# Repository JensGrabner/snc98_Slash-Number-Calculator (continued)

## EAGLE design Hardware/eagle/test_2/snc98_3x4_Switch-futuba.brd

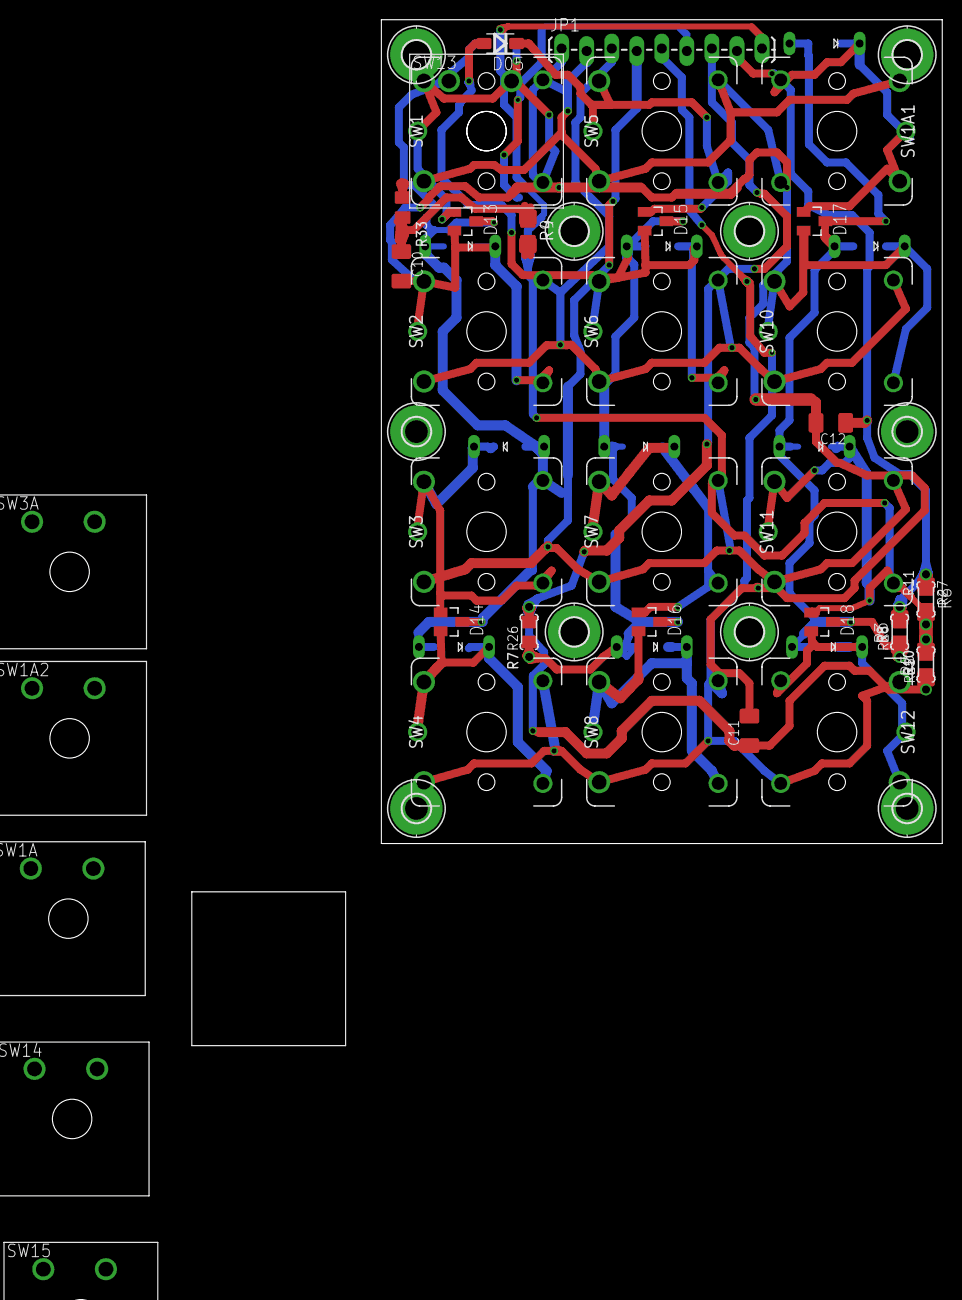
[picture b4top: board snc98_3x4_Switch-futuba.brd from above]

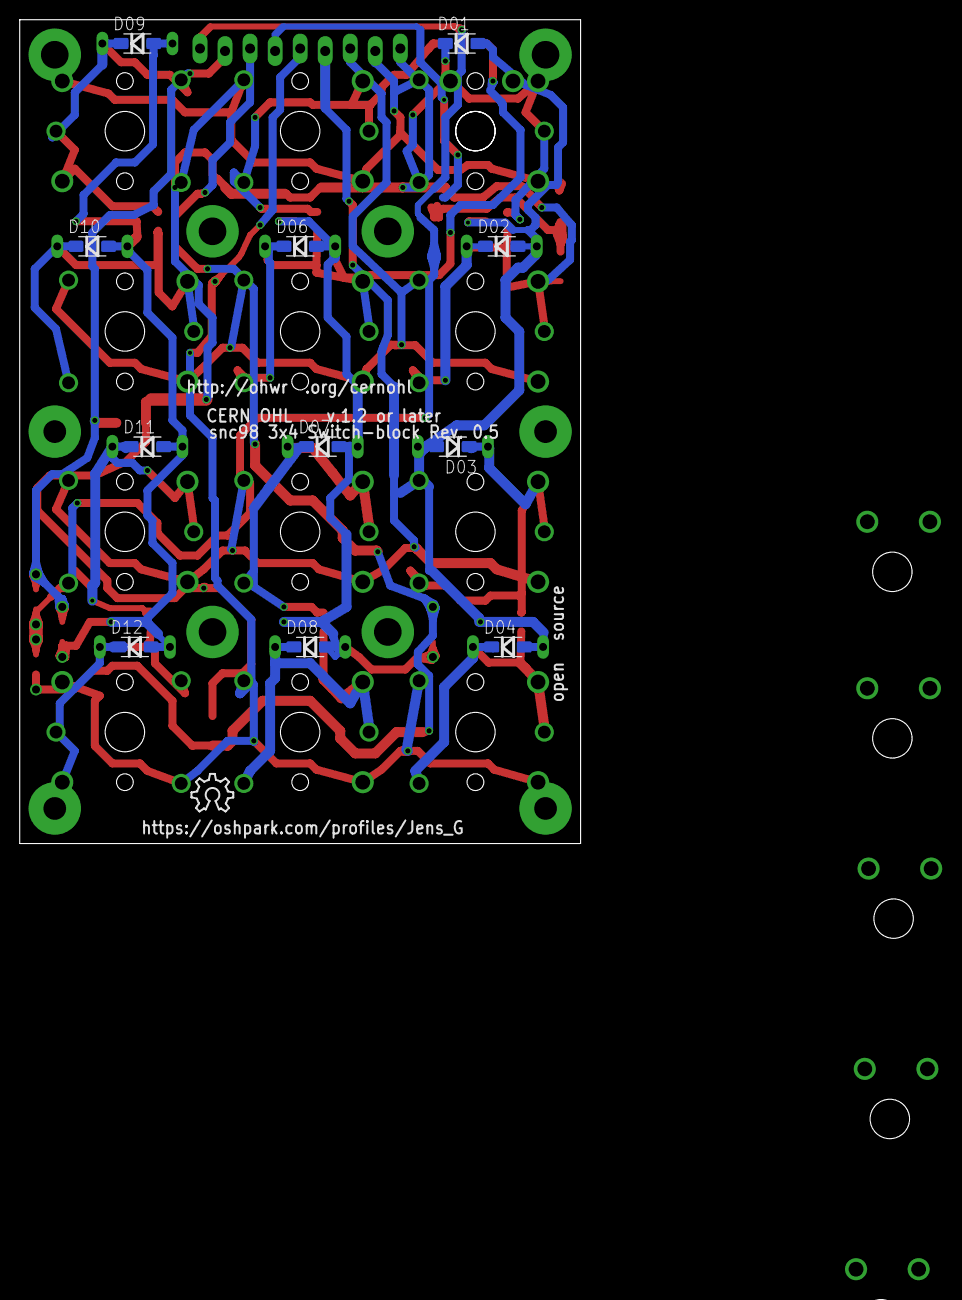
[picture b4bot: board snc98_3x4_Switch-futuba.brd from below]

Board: 2 copper layers, 56.9 x 83.6 mm, 75 parts (12 on the bottom side), 24 nets.

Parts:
C10, C11, C12: 15n; C1206K
D01, D02, D03, D04, D05, D06, D07, D08, D09: SD103AW-DIO; SOD-123F
D10, D11, D12: SD103CW; SOD-123F
D13, D14, D15, D16, D17, D18: BAT54A; SOT23
D19, D20, D21, D22, D23, D24, D25, D26, D27, D28: SD103C; 280MIL-TH
H1, H4, H5, H6, H7, H8: MOUNT-PAD-ROUND2.8; 2,8-PAD
H2, H3, H9, H10: MOUNT-PAD-ROUND2.3; 2,3-PAD
JP1: M09LOCK-LONGPADS; 1X09_LOCK_LONGPADS
LOGO1: OSHW_LOGO_8MILX0150-NT; OSHW_8X150_NOTEXT
R3: 6k8; R1206
R4, R5, R6: 27k; R1206
R7, R8, R33: 6k8; M0805
R9, R10, R11: 27k; M0805
R25, R27: 27k; 0204/5
R26, R28: 6k8; 0204/5
SW1, SW1A1, SW2, SW3, SW4, SW5, SW6, SW7, SW8, SW10, SW11, SW12: CHERRY_MX_WITH_FIXING_PINS; MX1A-XXNW
SW1A, SW1A2, SW3A, SW13, SW14, SW15: CHERRY_MX; MX1A-XXNN

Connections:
A2: C11.1, JP1.7, R5.1, R7.2, R10.1, R25.1, R26.2
A3: C12.1, JP1.8, R3.2, R6.1, R8.2, R11.1, R27.1, R28.2
AREF: R5.2, R6.2, R10.2, R11.2, R25.2, R27.2
A_2: D05.A, D06.A, D07.A, D08.A, D15.3, D16.3, D22.P$1, D23.P$1, D24.P$1, R7.1, R26.1
A_3: D09.A, D10.A, D11.A, D12.A, D17.3, D18.3, D25.P$1, D26.P$1, D27.P$1, D28.P$1, R3.1, R8.1, R28.1
C1: JP1.2, SW1.1, SW1.3, SW1A1.1, SW1A1.3, SW5.1, SW5.3
C2: JP1.3, SW2.1, SW2.3, SW6.1, SW6.3, SW10.1, SW10.3
C3: JP1.4, SW3.1, SW3.3, SW7.1, SW7.3, SW11.1, SW11.3
C4: JP1.5, SW4.1, SW4.3, SW8.1, SW8.3, SW12.1, SW12.3
GND: C10.2, C11.2, C12.2, JP1.1
unnamed: D04.C, D14.2, D21.P$2, SW4.2, SW4.4, SW4.5
unnamed: D01.C, D13.1, SW1.2, SW1.4, SW1.5
unnamed: D09.C, D17.1, D25.P$2, SW1A1.2, SW1A1.4, SW1A1.5
unnamed: D10.C, D17.2, D26.P$2, SW10.2, SW10.4, SW10.5
unnamed: D02.C, D13.2, D19.P$2, SW2.2, SW2.4, SW2.5
unnamed: D11.C, D18.1, D27.P$2, SW11.2, SW11.4, SW11.5
unnamed: D12.C, D18.2, D28.P$2, SW12.2, SW12.4, SW12.5
unnamed: D05.C, D15.1, SW5.2, SW5.4, SW5.5
unnamed: D06.C, D15.2, D22.P$2, SW6.2, SW6.4, SW6.5
unnamed: D07.C, D16.1, D23.P$2, SW7.2, SW7.4, SW7.5
unnamed: D08.C, D16.2, D24.P$2, SW8.2, SW8.4, SW8.5
unnamed: D03.C, D14.1, D20.P$2, SW3.2, SW3.4, SW3.5
S$5: JP1.9, R4.2
S$9: D02.A, D03.A, D04.A, D13.3, D14.3, D19.P$1, D20.P$1, D21.P$1

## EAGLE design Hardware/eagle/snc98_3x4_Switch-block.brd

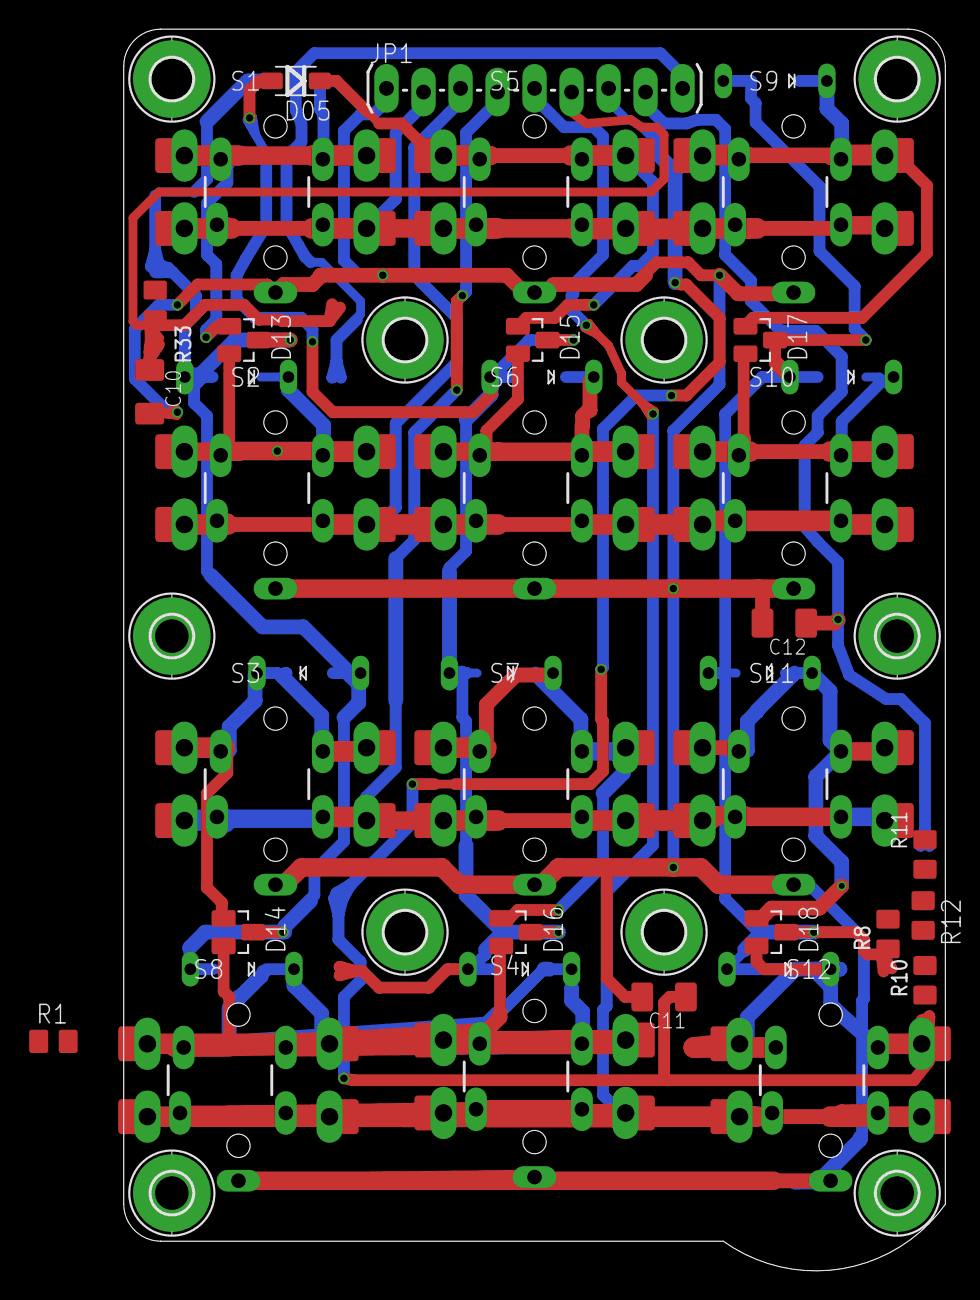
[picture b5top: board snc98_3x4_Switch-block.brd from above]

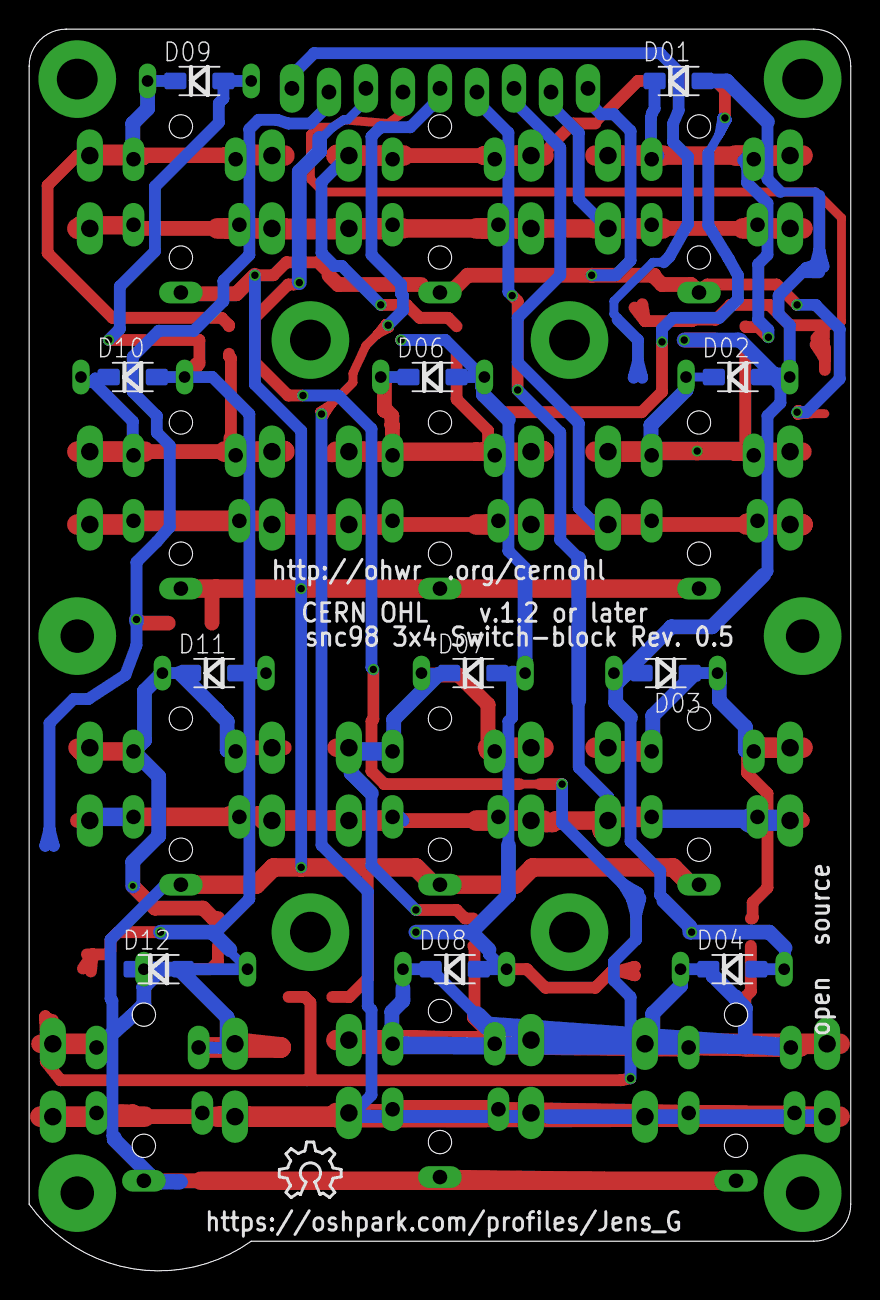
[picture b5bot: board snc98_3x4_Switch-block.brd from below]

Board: 2 copper layers, 56.4 x 85.2 mm, 61 parts (12 on the bottom side), 24 nets.

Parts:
C10, C11, C12: 15n; C1206K
D01, D02, D03, D04, D05, D06, D07, D08, D09: SD103AW-DIO; SOD-123F
D10, D11, D12: SD103CW; SOD-123F
D13, D14, D15, D16, D17, D18: BAT54A; SOT23
D19, D20, D21, D22, D23, D24, D25, D26, D27, D28: SD103C; 280MIL-TH
H1, H4, H5, H6, H7, H8: MOUNT-PAD-ROUND2.8; 2,8-PAD
H2, H3, H9, H10: MOUNT-PAD-ROUND2.3; 2,3-PAD
JP1: M09LOCK-LONGPADS; 1X09_LOCK_LONGPADS
LOGO1: OSHW_LOGO_8MILX0150-NT; OSHW_8X150_NOTEXT
R1, R8, R33: 6k8; M0805
R10, R11, R12: 27k; M0805
S1, S2, S3, S4, S5, S6, S7, S8, S9, S10, S11, S12: B3F-4150; TACTILE-PTH-12MM

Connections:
A1: C10.1, JP1.6, R12.1, R33.2
A2: C11.1, JP1.7, R1.2, R10.1
A3: C12.1, JP1.8, R8.2, R11.1
AREF: JP1.9, R10.2, R11.2, R12.2
A_1: D01.A, D02.A, D03.A, D04.A, D13.3, D14.3, D19.P$1, D20.P$1, D21.P$1, R33.1
A_2: D05.A, D06.A, D07.A, D08.A, D15.3, D16.3, D22.P$1, D23.P$1, D24.P$1, R1.1
A_3: D09.A, D10.A, D11.A, D12.A, D17.3, D18.3, D25.P$1, D26.P$1, D27.P$1, D28.P$1, R8.1
C1: JP1.2, S1.P$1, S1.P$2, S1.P$11, S1.P$12, S1.P$21, S1.P$22, S5.P$1, S5.P$2, S5.P$11, S5.P$12, S5.P$21, S5.P$22, S9.P$1, S9.P$2, S9.P$11, S9.P$12, S9.P$21, S9.P$22
C2: JP1.3, S2.P$1, S2.P$2, S2.P$11, S2.P$12, S2.P$21, S2.P$22, S6.P$1, S6.P$2, S6.P$11, S6.P$12, S6.P$21, S6.P$22, S10.P$1, S10.P$2, S10.P$11, S10.P$12, S10.P$21, S10.P$22
C3: JP1.4, S3.P$1, S3.P$2, S3.P$11, S3.P$12, S3.P$21, S3.P$22, S7.P$1, S7.P$2, S7.P$11, S7.P$12, S7.P$21, S7.P$22, S11.P$1, S11.P$2, S11.P$11, S11.P$12, S11.P$21, S11.P$22
C4: JP1.5, S4.P$1, S4.P$2, S4.P$11, S4.P$12, S4.P$21, S4.P$22, S8.P$1, S8.P$2, S8.P$11, S8.P$12, S8.P$21, S8.P$22, S12.P$1, S12.P$2, S12.P$11, S12.P$12, S12.P$21, S12.P$22
GND: C10.2, C11.2, C12.2, JP1.1, S1.P$15, S2.P$15, S3.P$15, S4.P$15, S5.P$15, S6.P$15, S7.P$15, S8.P$15, S9.P$15, S10.P$15, S11.P$15, S12.P$15
unnamed: D04.C, D14.2, D21.P$2, S4.P$3, S4.P$4, S4.P$13, S4.P$14, S4.P$23, S4.P$24
unnamed: D01.C, D13.1, S1.P$3, S1.P$4, S1.P$13, S1.P$14, S1.P$23, S1.P$24
unnamed: D09.C, D17.1, D25.P$2, S9.P$3, S9.P$4, S9.P$13, S9.P$14, S9.P$23, S9.P$24
unnamed: D10.C, D17.2, D26.P$2, S10.P$3, S10.P$4, S10.P$13, S10.P$14, S10.P$23, S10.P$24
unnamed: D02.C, D13.2, D19.P$2, S2.P$3, S2.P$4, S2.P$13, S2.P$14, S2.P$23, S2.P$24
unnamed: D11.C, D18.1, D27.P$2, S11.P$3, S11.P$4, S11.P$13, S11.P$14, S11.P$23, S11.P$24
unnamed: D12.C, D18.2, D28.P$2, S12.P$3, S12.P$4, S12.P$13, S12.P$14, S12.P$23, S12.P$24
unnamed: D05.C, D15.1, S5.P$3, S5.P$4, S5.P$13, S5.P$14, S5.P$23, S5.P$24
unnamed: D06.C, D15.2, D22.P$2, S6.P$3, S6.P$4, S6.P$13, S6.P$14, S6.P$23, S6.P$24
unnamed: D07.C, D16.1, D23.P$2, S7.P$3, S7.P$4, S7.P$13, S7.P$14, S7.P$23, S7.P$24
unnamed: D08.C, D16.2, D24.P$2, S8.P$3, S8.P$4, S8.P$13, S8.P$14, S8.P$23, S8.P$24
unnamed: D03.C, D14.1, D20.P$2, S3.P$3, S3.P$4, S3.P$13, S3.P$14, S3.P$23, S3.P$24

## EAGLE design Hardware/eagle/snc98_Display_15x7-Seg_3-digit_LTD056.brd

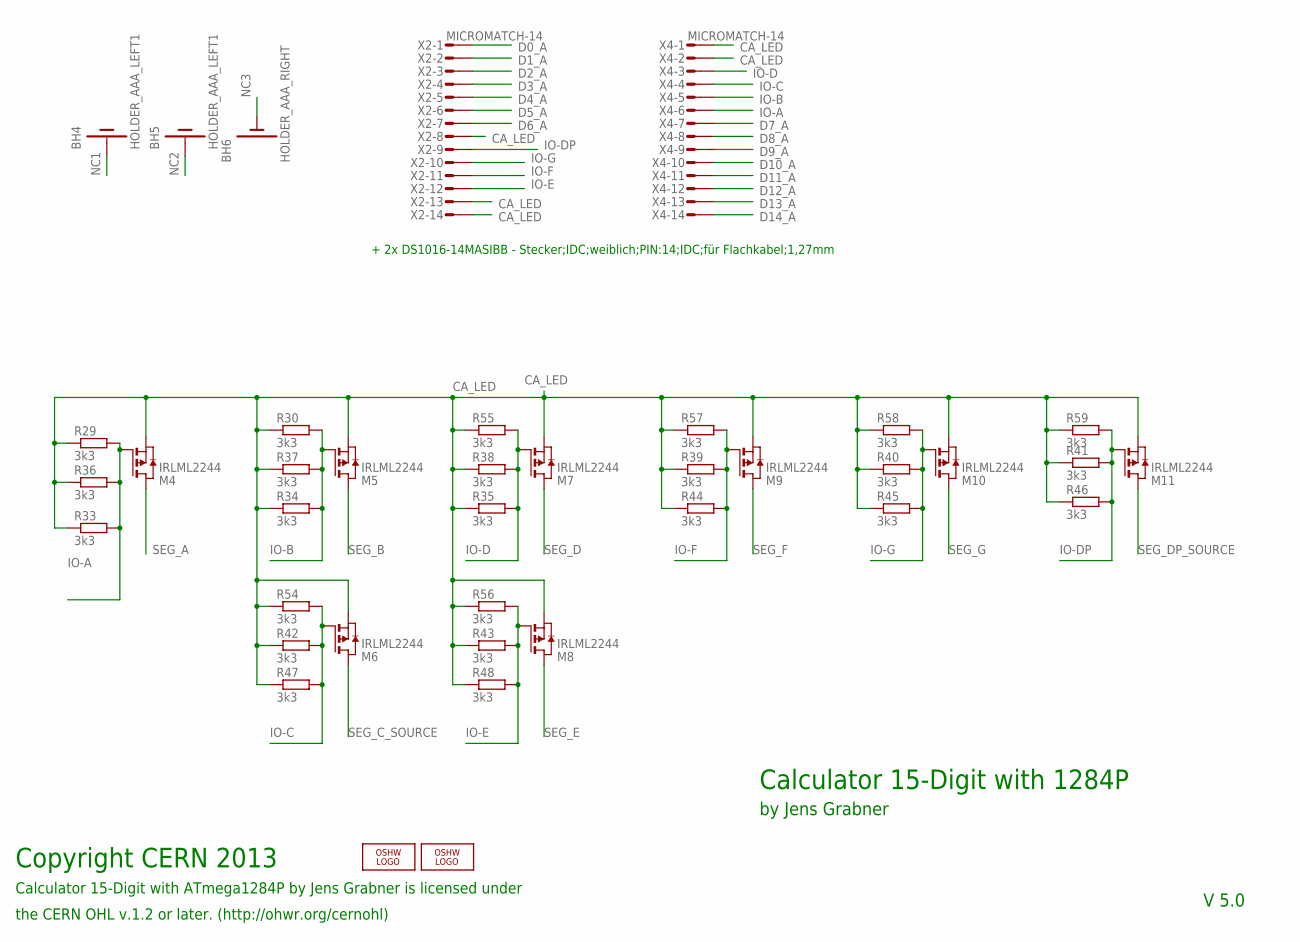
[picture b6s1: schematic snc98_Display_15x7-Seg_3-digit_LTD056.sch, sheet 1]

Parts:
BH4, BH5: HOLDER_AAA_LEFT1; BATTERY-AAA-LEFT
BH6: HOLDER_AAA_RIGHT; BATTERY-AAA-RIGHT
LOGO1: OSHW_LOGO_8MILX0150-NT; OSHW_8X150_NOTEXT
LOGO3: OSHW_LOGO_6MILX0100-NT; OSHW_6X100_NOTEXT
M4, M5, M6, M7, M8, M9, M10, M11: IRLML2244; SOT-23; MPN IRLML2244TRPBF
R29, R30, R54, R55, R56, R57, R58, R59: 3k3; 0204/5
R33, R34, R35, R44, R45, R46, R47, R48: 3k3; M0805
R36, R37, R38, R39, R40, R41, R42, R43: 3k3; R1206
X2, X4: MICROMATCH-14

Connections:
CA_LED: M4.2 (S), M5.2 (S), M6.2 (S), M7.2 (S), M8.2 (S), M9.2 (S), M10.2 (S), M11.2 (S), R29.1, R30.1, R33.1, R34.1, R35.1, R36.1, R37.1, R38.1, R39.1, R40.1, R41.1, R42.1, R43.1, R44.1, R45.1, R46.1, R47.1, R48.1, R54.1, R55.1, R56.1, R57.1, R58.1, R59.1, X2.8, X2.13, X2.14, X4.1, X4.2; also elsewhere on the board
D0_A: X2.1; also elsewhere on the board
D1_A: X2.2; also elsewhere on the board
D2_A: X2.3; also elsewhere on the board
D3_A: X2.4; also elsewhere on the board
D4_A: X2.5; also elsewhere on the board
D5_A: X2.6; also elsewhere on the board
D6_A: X2.7; also elsewhere on the board
D7_A: X4.7; also elsewhere on the board
D8_A: X4.8; also elsewhere on the board
D9_A: X4.9; also elsewhere on the board
D10_A: X4.10; also elsewhere on the board
D11_A: X4.11; also elsewhere on the board
D12_A: X4.12; also elsewhere on the board
D13_A: X4.13; also elsewhere on the board
D14_A: X4.14; also elsewhere on the board
IO-A: M4.1 (G), R29.2, R33.2, R36.2, X4.6
IO-B: M5.1 (G), R30.2, R34.2, R37.2, X4.5
IO-C: M6.1 (G), R42.2, R47.2, R54.2, X4.4
IO-D: M7.1 (G), R35.2, R38.2, R55.2, X4.3
IO-DP: M11.1 (G), R41.2, R46.2, R59.2, X2.9
IO-E: M8.1 (G), R43.2, R48.2, R56.2, X2.12
IO-F: M9.1 (G), R39.2, R44.2, R57.2, X2.11
IO-G: M10.1 (G), R40.2, R45.2, R58.2, X2.10
NC1: BH4.P1, BH4.P2, BH4.P3, BH4.P4
NC2: BH5.P1, BH5.P2, BH5.P3, BH5.P4
NC3: BH6.M1, BH6.M2, BH6.M3, BH6.M4
SEG_A: M4.3 (D); also elsewhere on the board
SEG_B: M5.3 (D); also elsewhere on the board
SEG_C_SOURCE: M6.3 (D); also elsewhere on the board
SEG_D: M7.3 (D); also elsewhere on the board
SEG_DP_SOURCE: M11.3 (D)
SEG_E: M8.3 (D); also elsewhere on the board
SEG_F: M9.3 (D); also elsewhere on the board
SEG_G: M10.3 (D); also elsewhere on the board

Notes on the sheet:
Calculator 15-Digit with 1284P
by Jens Grabner
V 5.0
Calculator 15-Digit with ATmega1284P by Jens Grabner is licensed under
Copyright CERN 2013
the CERN OHL v.1.2 or later. (http://ohwr.org/cernohl)
+ 2x DS1016-14MASIBB - Stecker;IDC;weiblich;PIN:14;IDC;für Flachkabel;1,27mm

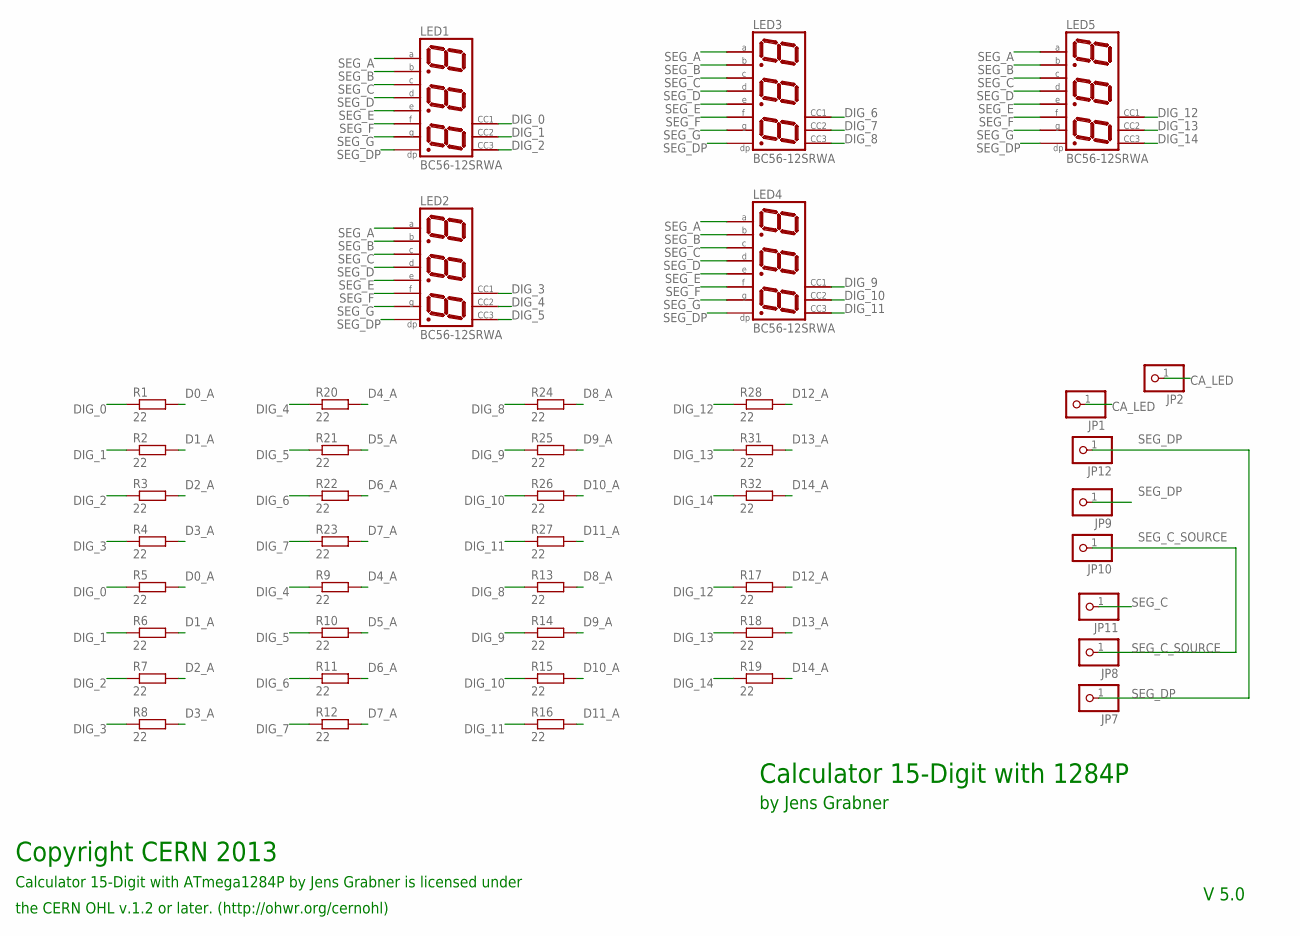
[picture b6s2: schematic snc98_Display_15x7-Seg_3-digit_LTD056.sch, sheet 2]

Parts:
JP1, JP2, JP7, JP8, JP9, JP10, JP11, JP12: PINHD-1X1; 1X01
LED1, LED2, LED3, LED4, LED5: BC56-12SRWA; BX56-12
R1, R2, R3, R4, R20, R21, R22, R23, R24, R25, R26, R27, R28, R31, R32: 22; R0805
R5, R6, R7, R8, R9, R10, R11, R12, R13, R14, R15, R16, R17, R18, R19: 22; R1210

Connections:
CA_LED: JP1.1, JP2.1; also elsewhere on the board
D0_A: R1.2, R5.2; also elsewhere on the board
D1_A: R2.2, R6.2; also elsewhere on the board
D2_A: R3.2, R7.2; also elsewhere on the board
D3_A: R4.2, R8.2; also elsewhere on the board
D4_A: R9.2, R20.2; also elsewhere on the board
D5_A: R10.2, R21.2; also elsewhere on the board
D6_A: R11.2, R22.2; also elsewhere on the board
D7_A: R12.2, R23.2; also elsewhere on the board
D8_A: R13.2, R24.2; also elsewhere on the board
D9_A: R14.2, R25.2; also elsewhere on the board
D10_A: R15.2, R26.2; also elsewhere on the board
D11_A: R16.2, R27.2; also elsewhere on the board
D12_A: R17.2, R28.2; also elsewhere on the board
D13_A: R18.2, R31.2; also elsewhere on the board
D14_A: R19.2, R32.2; also elsewhere on the board
DIG_0: LED1.12 (CA), R1.1, R5.1
DIG_1: LED1.9 (CA), R2.1, R6.1
DIG_2: LED1.8 (CA), R3.1, R7.1
DIG_3: LED2.12 (CA), R4.1, R8.1
DIG_4: LED2.9 (CA), R9.1, R20.1
DIG_5: LED2.8 (CA), R10.1, R21.1
DIG_6: LED3.12 (CA), R11.1, R22.1
DIG_7: LED3.9 (CA), R12.1, R23.1
DIG_8: LED3.8 (CA), R13.1, R24.1
DIG_9: LED4.12 (CA), R14.1, R25.1
DIG_10: LED4.9 (CA), R15.1, R26.1
DIG_11: LED4.8 (CA), R16.1, R27.1
DIG_12: LED5.12 (CA), R17.1, R28.1
DIG_13: LED5.9 (CA), R18.1, R31.1
DIG_14: LED5.8 (CA), R19.1, R32.1
SEG_A: LED1.11 (A), LED2.11 (A), LED3.11 (A), LED4.11 (A), LED5.11 (A); also elsewhere on the board
SEG_B: LED1.7 (B), LED2.7 (B), LED3.7 (B), LED4.7 (B), LED5.7 (B); also elsewhere on the board
SEG_C: JP11.1, LED1.4 (C), LED2.4 (C), LED3.4 (C), LED4.4 (C), LED5.4 (C)
SEG_C_SOURCE: JP8.1, JP10.1; also elsewhere on the board
SEG_D: LED1.2 (D), LED2.2 (D), LED3.2 (D), LED4.2 (D), LED5.2 (D); also elsewhere on the board
SEG_DP: JP7.1, JP9.1, JP12.1, LED1.3 (DP), LED2.3 (DP), LED3.3 (DP), LED4.3 (DP), LED5.3 (DP)
SEG_E: LED1.1 (E), LED2.1 (E), LED3.1 (E), LED4.1 (E), LED5.1 (E); also elsewhere on the board
SEG_F: LED1.10 (F), LED2.10 (F), LED3.10 (F), LED4.10 (F), LED5.10 (F); also elsewhere on the board
SEG_G: LED1.5 (G), LED2.5 (G), LED3.5 (G), LED4.5 (G), LED5.5 (G); also elsewhere on the board

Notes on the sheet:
Calculator 15-Digit with 1284P
by Jens Grabner
V 5.0
Calculator 15-Digit with ATmega1284P by Jens Grabner is licensed under
Copyright CERN 2013
the CERN OHL v.1.2 or later. (http://ohwr.org/cernohl)

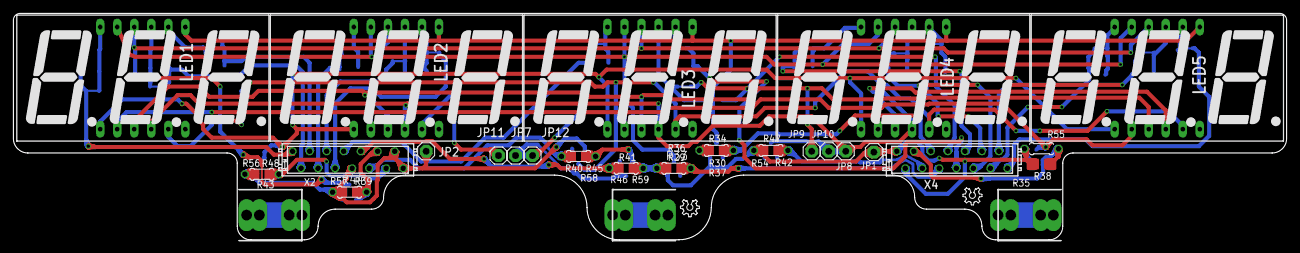
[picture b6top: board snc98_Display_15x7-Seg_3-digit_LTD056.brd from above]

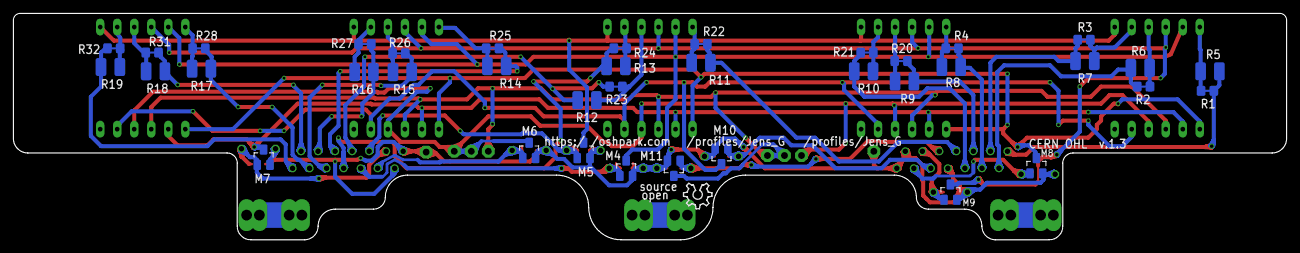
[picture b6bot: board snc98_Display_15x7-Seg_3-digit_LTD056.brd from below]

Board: 2 copper layers, 190.0 x 33.8 mm, 83 parts (39 on the bottom side), 51 nets.

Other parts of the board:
LOGO2: OSHW_LOGO_6MILX0100-NT; OSHW_6X100_NOTEXT

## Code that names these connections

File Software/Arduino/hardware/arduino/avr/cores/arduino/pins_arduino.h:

//
//
// Pins definitions for Goldilocks 1284P
// Original file from Maniacbug's Mighty-1284 core
// This version by Phillip Stevens (1st June 2013)
//
//

#ifndef Pins_Arduino_h
#define Pins_Arduino_h

#include <avr/pgmspace.h>

//                    ATMEL ATMEGA1284P on Goldilocks
//                    Actual implementation with VQFN
//
//                               +---\/---+
//            PCINT8 (D14) PB0  1|        |40  PA0 (AI 0 / D24) PCINT0
//            PCINT9 (D15) PB1  2|        |39  PA1 (AI 1 / D25) PCINT1
//      PCINT10/INT2 (D 8) PB2  3|        |38  PA2 (AI 2 / D26) PCINT2
//      PCINT11/OC0A*(D 9) PB3  4|        |37  PA3 (AI 3 / D27) PCINT3
//   PCINT12/0C0B/SS*(D10) PB4  5|        |36  PA4 (AI 4 / D28) PCINT4
//      PCINT13/MOSI (D11) PB5  6|        |35  PA5 (AI 5 / D29) PCINT5
// PCINT14/OC3A/MISO*(D12) PB6  7|        |34  PA6 (AI 6 / D30) PCINT6
//  PCINT15/OC3B/SCK*(D13) PB7  8|        |33  PA7 (AI 7 / D31) PCINT7
//                         RST  9|        |32  AREF
//                         VCC 10|        |31  GND 
//                         GND 11|        |30  AVCC
//                       XTAL2 12|        |29  PC7 (D23) TOSC2/PCINT23
//                       XTAL1 13|        |28  PC6 (D22) TOSC1/PCINT22
//       PCINT24/RX0 (D 0) PD0 14|        |27  PC5 (D21) TDI/PCINT21
//       PCINT25/TX0 (D 1) PD1 15|        |26  PC4 (D20) TDO/PCINT20
//  PCINT26/INT0/RX1 (D 2) PD2 16|        |25  PC3 (D19) TMS/PCINT19
//  PCINT27/INT1/TX1 (D 3) PD3 17|        |24  PC2 (D18) TCK/PCINT18
//      PCINT28/OC1B*(D 4) PD4 18|        |23  PC1 (D17) SDA/PCINT17
//      PCINT29/OC1A*(D 5) PD5 19|        |22  PC0 (D16) SCL/PCINT16
//      PCINT30/OC2B*(D 6) PD6 20|        |21  PD7 (D 7)*OC2A/PCINT31
//                               +--------+
// * = PWM capable pin
// TOSCn = RTC Crystal pinout
// TCK/TMS/TDO/TDI = JTAG pinout

/*                       
                         PCICR
   PCINT7-0:   D31-24  : bit 0   
   PCINT15-8:  D15- 8  : bit 1
   PCINT23-16: D23-16  : bit 2
   PCINT31-24: D 7- 0  : bit 3
*/

#define NUM_DIGITAL_PINS            32
#define NUM_ANALOG_INPUTS           8
#define analogInputToDigitalPin(p)  ((p < NUM_ANALOG_INPUTS) ? (p) + 24 : -1)

#define digitalPinHasPWM(p)         ((p) == 4 || (p) == 5 || (p) == 6 || (p) == 7 || (p) == 9 || (p) == 10 || (p) == 12 || (p) == 13)

static const uint8_t SS   = 10;
static const uint8_t MOSI = 11;
static const uint8_t MISO = 12;
static const uint8_t SCK  = 13;

static const uint8_t SDA = 17;
static const uint8_t SCL = 16;
static const uint8_t LED = 13;

static const uint8_t A0 = 24;
static const uint8_t A1 = 25;
static const uint8_t A2 = 26;
static const uint8_t A3 = 27;
static const uint8_t A4 = 28;
static const uint8_t A5 = 29;
static const uint8_t A6 = 30;
static const uint8_t A7 = 31;

#define digitalPinToPCICR(p)    (((p) >= 0 && (p) < NUM_DIGITAL_PINS) ? (&PCICR) : ((uint8_t *)0))
#define digitalPinToPCICRbit(p) (((p) <= 7) ? 3 : (((p) <= 15) ? 1 : (((p) <= 23) ? 2 : 0)))
#define digitalPinToPCMSK(p)    (((p) <= 7) ? (&PCMSK3) : (((p) <= 15) ? (&PCMSK1) : (((p) <= 23) ? (&PCMSK2) : (&PCMSK0) )))

// The special case here, created by keeping the SPI interface on Arduino Uno pin numbering.
#define digitalPinToPCMSKbit(p) (((p) > 7 && (p) < 16) ? (((p) < 14 ? (p)+2 : (p)-6) % 8) : ((p) % 8))

#ifdef ARDUINO_MAIN

#define PA 1
#define PB 2
#define PC 3
#define PD 4

// these arrays map port names (e.g. port B) to the
// appropriate addresses for various functions (e.g. reading
// and writing)
const uint16_t PROGMEM port_to_mode_PGM[] =
{
	NOT_A_PORT,
	(uint16_t) &DDRA,
	(uint16_t) &DDRB,
	(uint16_t) &DDRC,
	(uint16_t) &DDRD,
};

const uint16_t PROGMEM port_to_output_PGM[] =
{
	NOT_A_PORT,
	(uint16_t) &PORTA,
	(uint16_t) &PORTB,
	(uint16_t) &PORTC,
	(uint16_t) &PORTD,
};

const uint16_t PROGMEM port_to_input_PGM[] =
{
	NOT_A_PORT,
	(uint16_t) &PINA,
	(uint16_t) &PINB,
	(uint16_t) &PINC,
	(uint16_t) &PIND,
};

const uint8_t PROGMEM digital_pin_to_port_PGM[] =
{
	PD, /* 0 */
	PD,
	PD,
	PD,
	PD,
	PD,
	PD,
	PD,
	PB, /* 8 */
	PB,
	PB,
	PB,
	PB,
	PB,
	PB,
	PB,
	PC, /* 16 */
	PC,
	PC,
	PC,
	PC,
	PC,
   	PC,
	PC,
	PA, /* 24 */
	PA,
	PA,
	PA,
	PA,
	PA,
	PA,
	PA  /* 31 */
};

const uint8_t PROGMEM digital_pin_to_bit_mask_PGM[] =
{
	_BV(0), /* 0, port D */
	_BV(1),
	_BV(2),
	_BV(3),
	_BV(4),
	_BV(5),
	_BV(6),
	_BV(7),
	_BV(2), /* 8, port B */
	_BV(3),
	_BV(4),
	_BV(5),
	_BV(6),
	_BV(7),
	_BV(0),
	_BV(1),
	_BV(0), /* 16, port C */
	_BV(1),
	_BV(2),
	_BV(3),
	_BV(4),
	_BV(5),
	_BV(6),
	_BV(7),
	_BV(0), /* 24, port A */
	_BV(1),
	_BV(2),
	_BV(3),
	_BV(4),
	_BV(5),
	_BV(6),
	_BV(7)
};

const uint8_t PROGMEM digital_pin_to_timer_PGM[] =
{
	NOT_ON_TIMER, 	/* 0  - PD0 */
	NOT_ON_TIMER, 	/* 1  - PD1 */
	NOT_ON_TIMER, 	/* 2  - PD2 */
	NOT_ON_TIMER, 	/* 3  - PD3 */
	TIMER1B,     	/* 4  - PD4 */
	TIMER1A,     	/* 5  - PD5 */
	TIMER2B,     	/* 6  - PD6 */
	TIMER2A,     	/* 7  - PD7 */

	NOT_ON_TIMER, 	/* 8  - PB2 */
	TIMER0A,     	/* 9  - PB3 */
	TIMER0B,        /* 10 - PB4 */
	NOT_ON_TIMER, 	/* 11 - PB5 */
	TIMER3A,        /* 12 - PB6 */
	TIMER3B,        /* 13 - PB7 */
	NOT_ON_TIMER, 	/* 14 - PB0 */
	NOT_ON_TIMER, 	/* 15 - PB1 */	

	NOT_ON_TIMER, 	/* 16 - PC0 */
	NOT_ON_TIMER,   /* 17 - PC1 */
	NOT_ON_TIMER,   /* 18 - PC2 */
	NOT_ON_TIMER,   /* 19 - PC3 */
	NOT_ON_TIMER,   /* 20 - PC4 */
	NOT_ON_TIMER,   /* 21 - PC5 */
	NOT_ON_TIMER,   /* 22 - PC6 */
	NOT_ON_TIMER,   /* 23 - PC7 */
	
	NOT_ON_TIMER,   /* 24 - PA0 */
	NOT_ON_TIMER,   /* 25 - PA1 */
	NOT_ON_TIMER,   /* 26 - PA2 */
	NOT_ON_TIMER,   /* 27 - PA3 */
	NOT_ON_TIMER,   /* 28 - PA4 */
	NOT_ON_TIMER,   /* 29 - PA5 */
	NOT_ON_TIMER,   /* 30 - PA6 */
	NOT_ON_TIMER    /* 31 - PA7 */
};

#endif // ARDUINO_MAIN

#endif // Pins_Arduino_h
// vim:ai:cin:sts=2 sw=2 ft=cpp

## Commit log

2016-03-16 Initial Release 0.2g
    .. this is a Beginning
2016-03-16 :octocat: Added .gitattributes & .gitignore files
2016-03-24 change switch from x^3 to INT and invers
2016-03-24 change "SM" to "Min"
2016-03-26 Doku "Switch_mechanical"
2016-04-01 Switch_Layout - smal changes on Layout
2016-04-10 add Display rotate
2016-04-21 Layout Switch change - Intg.Fra - to - Ip.Fp -
2016-04-26 Switch-block added
2016-05-30 Switch-block changed Rev.02
2016-06-08 Switch-block Filter added
2016-06-09 New Picture "Switch mechanical"
2016-06-15 PCB_Display_make
2016-07-17 Debug_Level 13: - Protokoll Statepoint
2016-07-19 Debuglevel 13 - Protokoll Statepoint
2016-07-20 PCB_Display_cleanup
2016-07-21 Optiboot_6
2016-08-16 snc98_Display_15x7-Segment_LED_v2
2016-09-27 new Switch Layout - with Kipptaster
2016-11-08 AVRational mul(); add(); div_x()
2017-01-27 MR(); MS(); M+=(); Display Status
    Display whe to or more switch pressed.
2017-02-26 Keyswitch - Sort - less Memory use
2017-03-07 RingBufCPP added
2017-03-27 sqrt() - 18-Digit
2017-04-14 New Hardware Design V0.4
2017-05-02 New Hardware Design V0.4a
2017-05-05 itoa_(8, 16, 32, 64-bit)
2017-05-06 itoa_() tested !
2017-05-09 runtime optimizing: itoa_()
2017-05-09 Test_itoa_ljust - initial
2017-05-11 Clean itoa_ljust Copyright
2017-05-13 itoa_ljust w/ default: switch-case
2017-05-31 Cleanup - Source
2017-06-20 Display .. 5x LTD040AUE-101A 3-digit_Display
2017-08-15 snc98_main_cpu V1.0
2017-09-30 (+ - * /) with 2 Numbers
2017-10-27 new Reset on Main:cpu
2017-11-01 add Iterated Means (AM) (GM) (HM)
2017-11-09 add Inter_part + Floating_par
2017-11-17 _x^3_ init
2017-11-22 Main_cpu_rev_0.95 - Add Onewire DS18B20
2017-12-01 Initial int96 Format
2017-12-03 speed_up itoa_ljust
2017-12-07 New Release int96_a itoa_ljust
2017-12-16 AGM - Arithmetic Geometric Mean added
2017-12-26 new Switch_mechanical.pdf
2018-01-28 fine with 2 numbers
2018-02-17 Add new Function: mod (modular)
2018-03-12 Work like WIN_7 Calculator in "Standard Mode"
2018-04-18 Version 4 mechanical change
2018-04-18 Switch_mechanical.pdf new
2018-04-24 Final_PCB_V4
2018-05-01 new keyboard plate
2018-05-31 V 5.0 Hardware - Design
2018-06-24 add Memory+ for all Numbers
2018-07-11 sci-Mode works - with 39 Numbers
2018-07-27 add function cbrt() - cube root
2018-09-24 add function ln() - natural log
2018-09-28 log(x,b) log(x) to base (b) added
2018-10-08 2^x, a^x, e^x, 10^x added
2018-11-04 add .. Factorial Function n!
2018-12-03 PCB cleaning V1.1
2019-01-02 Create LICENSE
2019-01-14 sinh()_cosh()_tanh() added
2019-02-03 PCB - add Tear Drop
2019-02-19 add - atanh()
2019-03-04 Gerber file added
2019-04-03 more accurate Factorial Function n!
2019-04-07 Gamma(x) = (x-1)! .. 0 < x <= 72
2019-09-02 add_sinus_0-45_Deg
2019-09-07 Update snc98.ino
    sin_cos_tan_01
2019-09-22 powx_with_integer
    a^x, 2^x, e^x, 10^. If x = integer than multiplication with the exponent. Is quicker and more accurat.
2019-10-02 log_new_algorithm
    400ms per Value
2019-10-09 atan initial
    not finished yet
2019-10-11 atan(x) full range
    good quality - atan(x)
2019-10-15 int96_a correction
2019-10-16 int96_a correction
    input and output from int32_t int64_t checked.
2019-10-25 change_to_6mm_taktile_switch
2019-11-17 cleanup_PCB
2019-11-24 better factorial
2019-12-02 asin_acos_initial_01
2019-12-09 atan_02
    atan with Range reduction 0.3 .. 0.7
2019-12-15 Reduce_Number corr_01
2019-12-21 cleanup 02
    div_x(const) --> const_div_x
    min_x(x) --> add ..
2020-03-04 cbrt_int96
    cbrt added
2020-03-26 New_PCB
2020-04-10 Repeating_Decimals_input
2020-04-11 repeated_decimals_01
2020-04-12 qbrt_update
2020-04-13 qbrt_96bit_less_time
2020-04-16 int96_a Modulus() .. update
    division with uint64_t operation
2020-04-23 cbrt_clean
2020-04-28 log_() more accurat
2020-05-03 exp2 little more accurate
2020-05-08 better_logarithm
2020-05-10 log2 update
2020-05-11 log2 best aproximation
2020-05-27 BOM_all
2020-09-10 add factorial() - today from -72 to +72.
    add factorial() - today from -72 to +72.
2020-09-10 update factural
2020-09-20 M+ M- Mx M/ -- added
    Initial: M+ M- Mx M/
2020-11-22 add_mul_spezial()
    add_mul_spezial()
2021-01-03 add_prozent
2021-01-26 log binary - new algorithm
2021-01-29 exp(x) new algorithm
2021-02-12 gamma - best 01
2021-03-06 add BootLoader
2021-03-10 add bootloader
    xxx
2021-03-25 update 02
2021-03-29 "show" Matisse 14-digit added
2021-03-29 show 14-digit added
2021-04-04 add Doku cordic
    xxx
2021-04-07 int96.cpp - optimized
2021-05-02 MCP9808 added
2021-05-16 uint32_t sqrt(uint64_t num)
    new sqrt for integer
2021-06-10 Ratio32 initial
2021-06-25 add BitBool
2021-11-27 add Dokument "The_flipped_continued_fraction.pdf"
2022-08-05 Difﬁcult_problems Dokument
